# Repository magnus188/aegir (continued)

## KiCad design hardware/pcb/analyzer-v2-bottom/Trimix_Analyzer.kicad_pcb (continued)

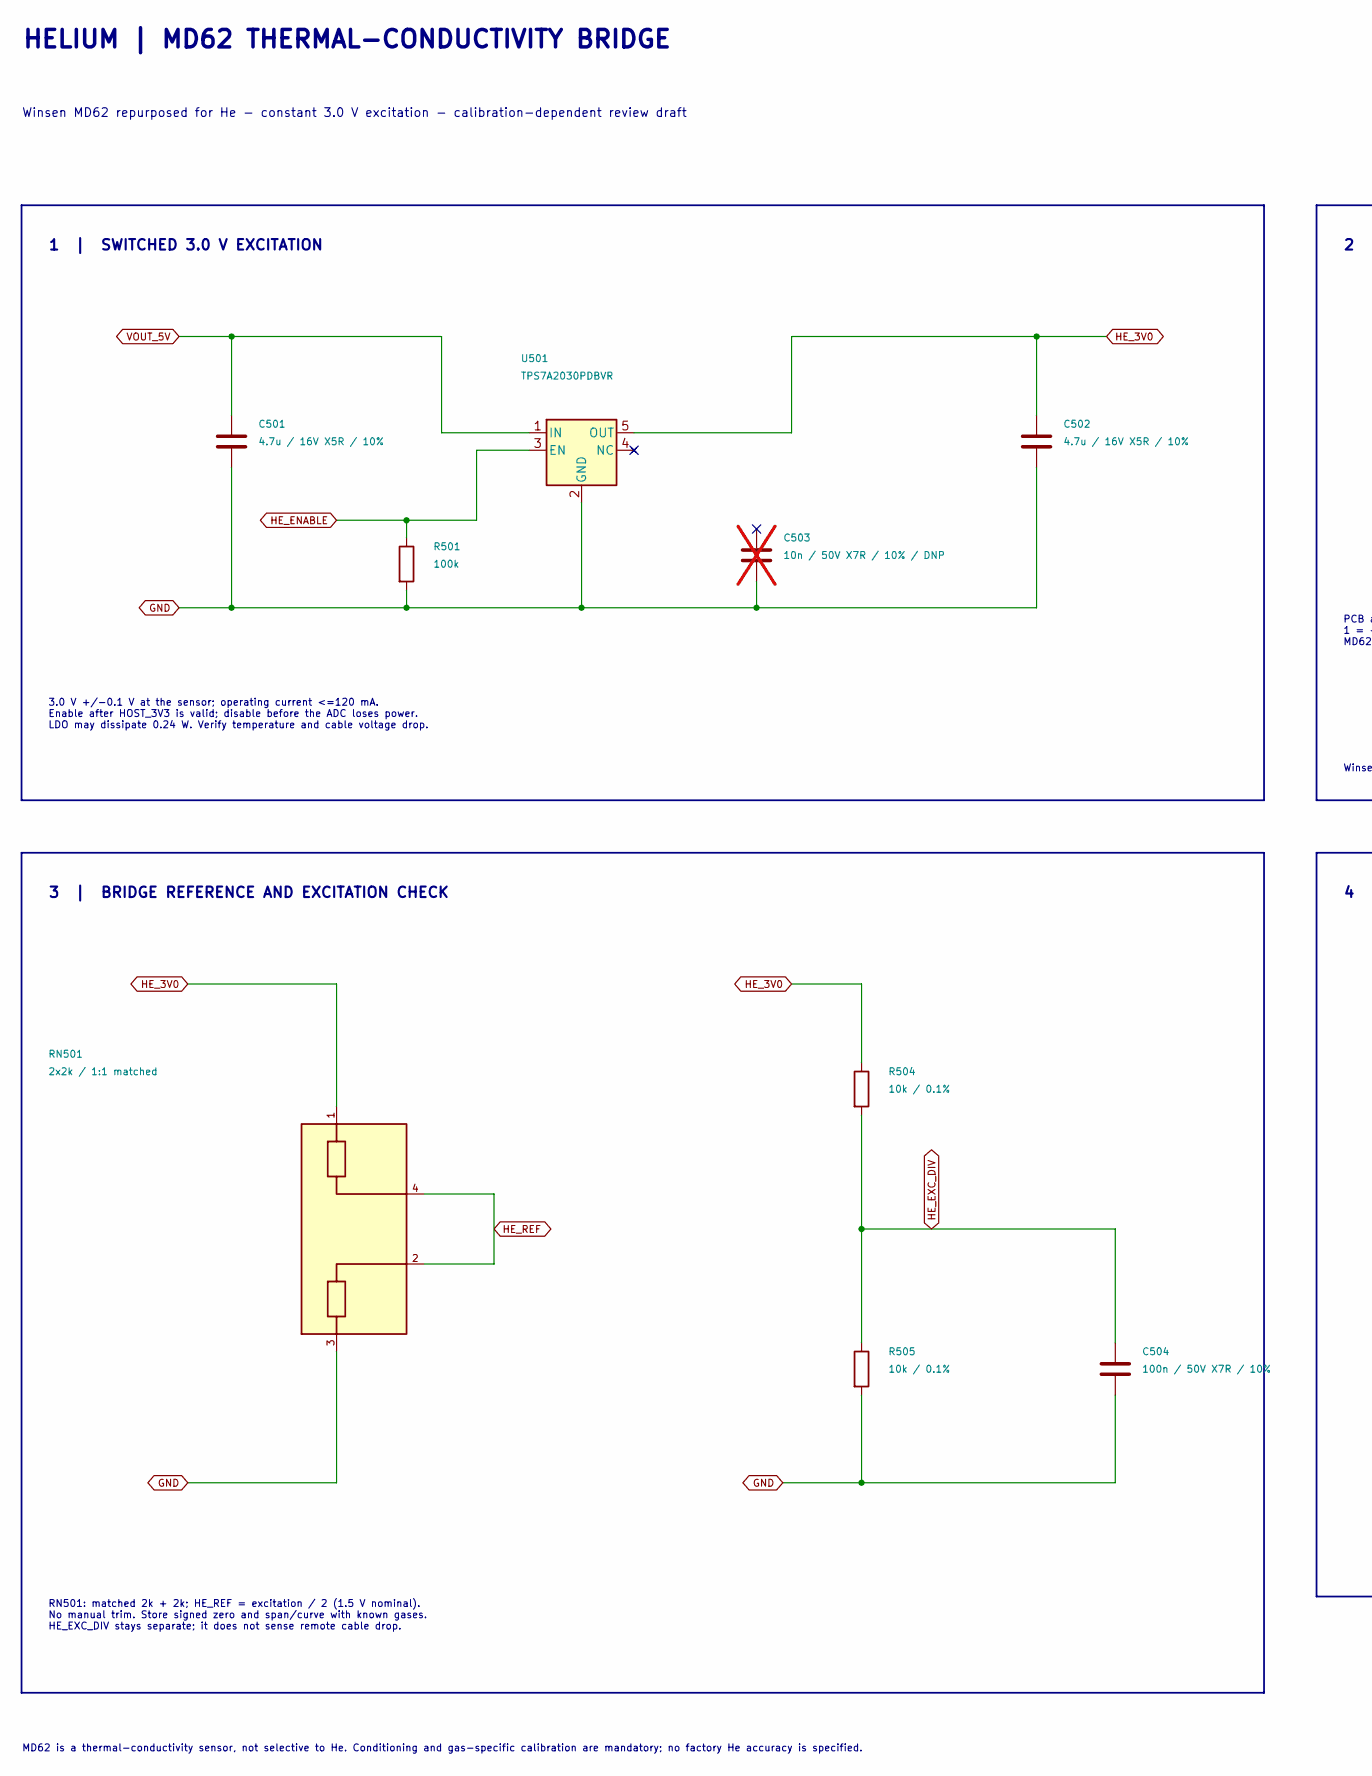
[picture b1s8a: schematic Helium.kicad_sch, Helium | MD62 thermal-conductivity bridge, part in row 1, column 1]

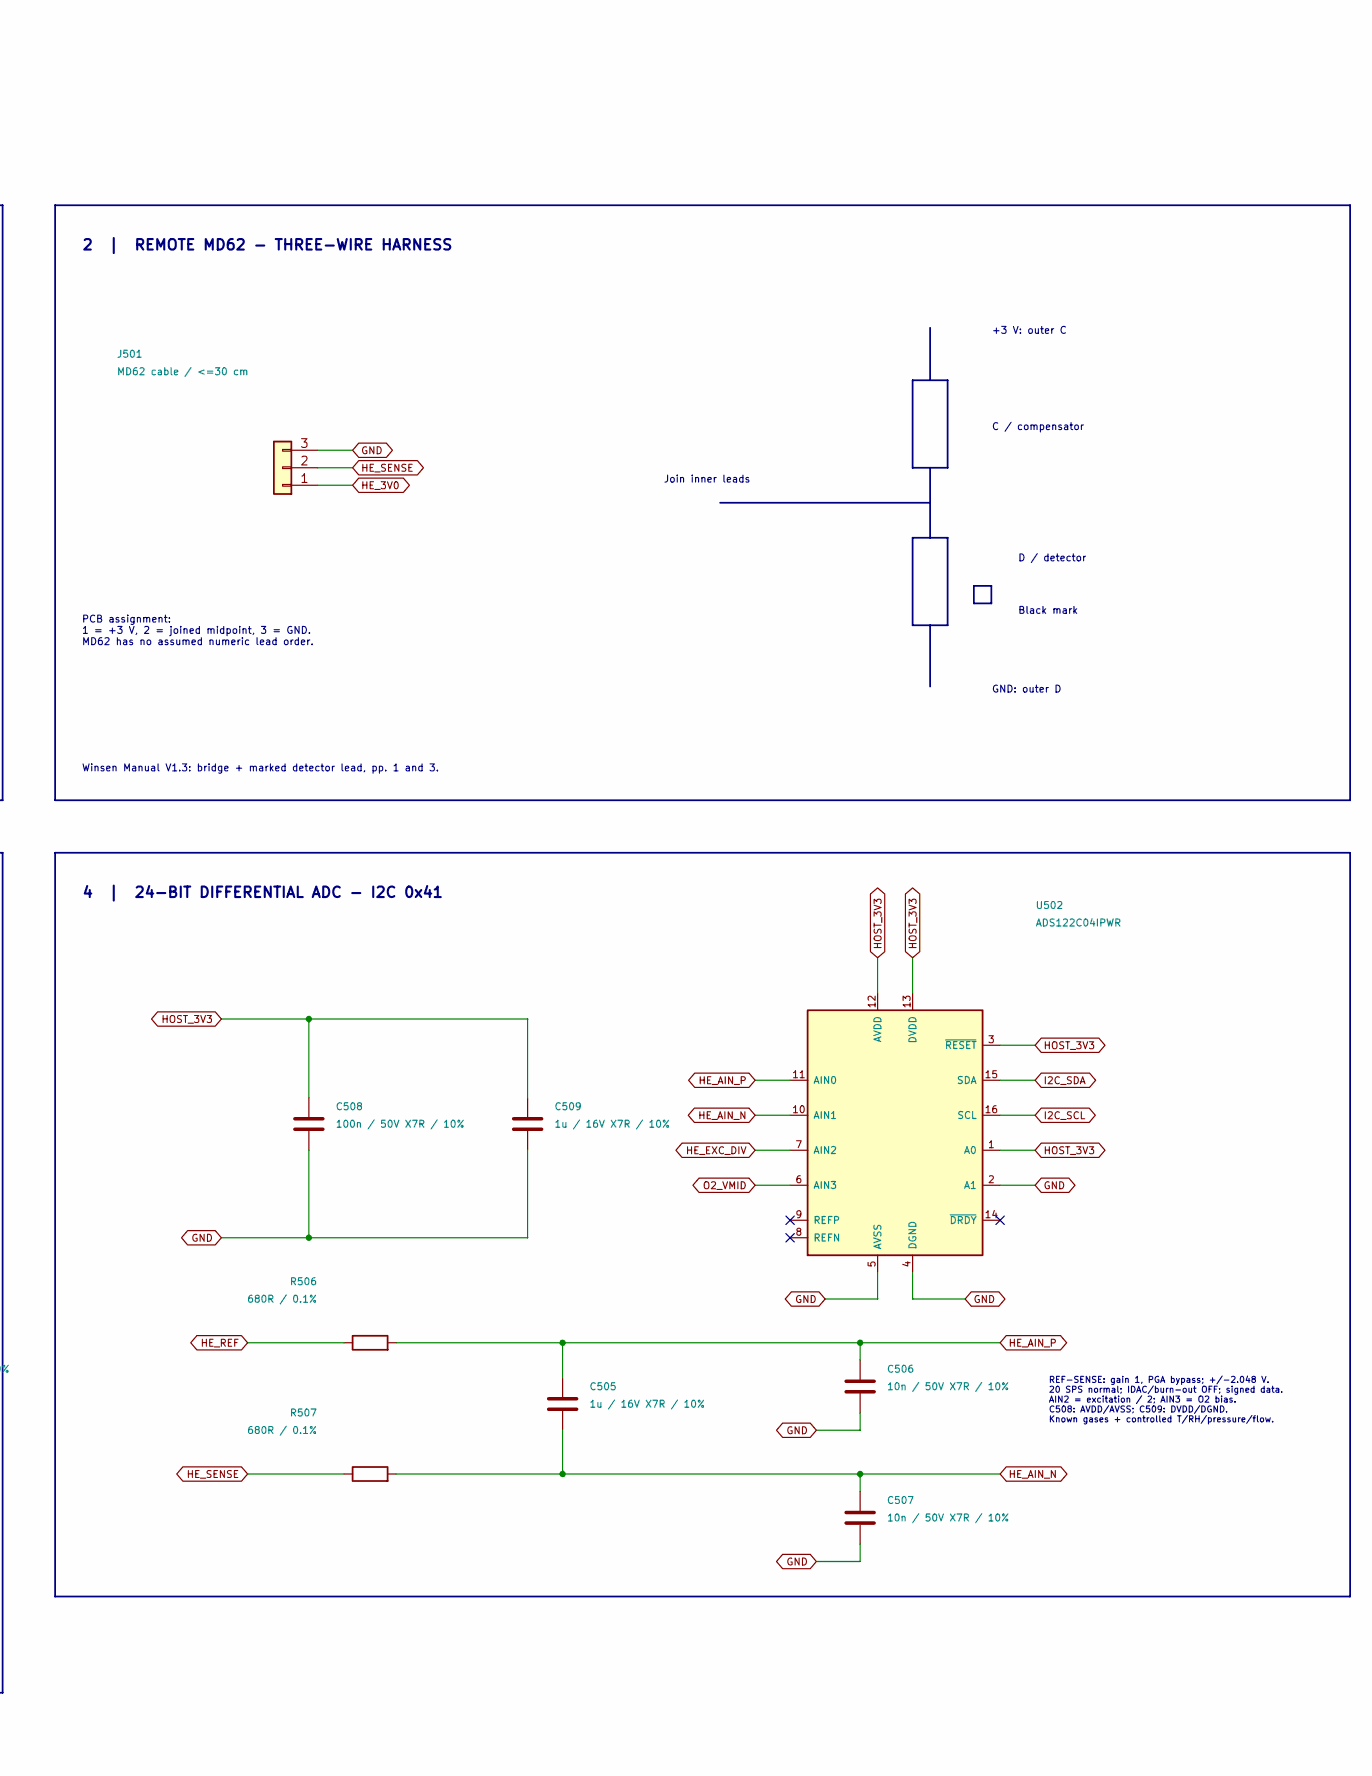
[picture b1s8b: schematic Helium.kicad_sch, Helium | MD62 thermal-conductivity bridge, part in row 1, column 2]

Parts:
C501, C502: 4.7u / 16V X5R / 10%; C_0603_1608Metric; MPN C1608X5R1C475K080AC
C503: 10n / 50V X7R / 10% / DNP; C_0603_1608Metric; MPN C1608X7R1H103K080AA; not fitted
C504, C508: 100n / 50V X7R / 10%; C_0603_1608Metric; MPN C1608X7R1H104K080AA
C505, C509: 1u / 16V X7R / 10%; C_0603_1608Metric; MPN C0603C105K4RACTU
C506, C507: 10n / 50V X7R / 10%; C_0603_1608Metric; MPN C1608X7R1H103K080AA
J501: MD62 cable / <=30 cm; PinHeader_1x03_P2.54mm_Vertical; MPN M20-9990346
R501: 100k; R_0603_1608Metric; MPN RC0603FR-07100KL
R504, R505: 10k / 0.1%; R_0603_1608Metric; MPN RT0603BRD0710KL
R506, R507: 680R / 0.1%; R_0603_1608Metric; MPN RT0603BRD07680RL
RN501: 2x2k / 1:1 matched; Vishay_ACAS0606_AT_IEC; MPN ACASN2001U2001P1AT
U501: TPS7A2030PDBVR; SOT-23-5; MPN TPS7A2030PDBVR
U502: ADS122C04IPWR; TSSOP-16_4.4x5mm_P0.65mm; MPN ADS122C04IPWR

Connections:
GND: C501.2, C502.2, C503.2, C504.2, C506.2, C507.2, C508.2, C509.2, J501.3, R501.2, R505.2, RN501.3 (R2.2), U501.2 (GND), U502.2 (A1), U502.4 (DGND), U502.5 (AVSS); also elsewhere on the board
HE_3V0: C502.1, J501.1, R504.1, RN501.1 (R1.1), U501.5 (OUT); also elsewhere on the board
HE_AIN_N: C505.2, C507.1, R507.2, U502.10 (AIN1)
HE_AIN_P: C505.1, C506.1, R506.2, U502.11 (AIN0)
HE_ENABLE: R501.1, U501.3 (EN); also elsewhere on the board
HE_EXC_DIV: C504.1, R504.2, R505.1, U502.7 (AIN2)
HE_REF: R506.1, RN501.2 (R2.1), RN501.4 (R1.2)
HE_SENSE: J501.2, R507.1; also elsewhere on the board
HOST_3V3: C508.1, C509.1, U502.1 (A0), U502.3 (~RESET), U502.12 (AVDD), U502.13 (DVDD); also elsewhere on the board
I2C_SCL: U502.16 (SCL); also elsewhere on the board
I2C_SDA: U502.15 (SDA); also elsewhere on the board
O2_VMID: U502.6 (AIN3); also elsewhere on the board
VOUT_5V: C501.1, U501.1 (IN); also elsewhere on the board

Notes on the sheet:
3.0 V +/-0.1 V at the sensor; operating current <=120 mA. Enable after HOST_3V3 is valid; disable before the ADC loses power. LDO may dissipate 0.24 W. Verify temperature and cable voltage drop.
D / detector
Black mark
REF-SENSE: gain 1, PGA bypass; +/-2.048 V. 20 SPS normal; IDAC/burn-out OFF; signed data. AIN2 = excitation / 2; AIN3 = O2 bias. C508: AVDD/AVSS; C509: DVDD/DGND. Known gases + controlled T/RH/pressure/flow.
RN501: matched 2k + 2k; HE_REF = excitation / 2 (1.5 V nominal). No manual trim. Store signed zero and span/curve with known gases. HE_EXC_DIV stays separate; it does not sense remote cable drop.
Winsen MD62 repurposed for He - constant 3.0 V excitation - calibration-dependent review draft
Join inner leads
C / compensator
2 | REMOTE MD62 - THREE-WIRE HARNESS
4 | 24-BIT DIFFERENTIAL ADC - I2C 0x41
MD62 is a thermal-conductivity sensor, not selective to He. Conditioning and gas-specific calibration are mandatory; no factory He accuracy is specified.
+3 V: outer C
PCB assignment: 1 = +3 V, 2 = joined midpoint, 3 = GND. MD62 has no assumed numeric lead order.
HELIUM | MD62 THERMAL-CONDUCTIVITY BRIDGE
GND: outer D
1 | SWITCHED 3.0 V EXCITATION
Winsen Manual V1.3: bridge + marked detector lead, pp. 1 and 3.
3 | BRIDGE REFERENCE AND EXCITATION CHECK

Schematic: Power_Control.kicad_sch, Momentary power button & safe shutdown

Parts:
C801, C802: 100n / 50V X7R / 10%; C_0603_1608Metric; MPN C1608X7R1H104K080AA
C803: 33n / 50V X7R / 10%; C_0805_2012Metric; MPN C0805C333K5RACTU
C804: 1u / 16V X7R / 10%; C_0603_1608Metric; MPN C0603C105K4RACTU
J801: POWER BUTTON / 1NO; PinHeader_1x02_P2.54mm_Vertical; MPN M20-9990246
J802: BUTTON LED +/-; PinHeader_1x02_P2.54mm_Vertical; MPN M20-9990246
R801: 5.1k; R_0603_1608Metric; MPN RC0603FR-075K1L
R802: 10k; R_0603_1608Metric; MPN RC0603FR-0710KL
R803: 100k; R_0603_1608Metric; MPN RC0603FR-07100KL
R804: 1k / DNP; R_0603_1608Metric; MPN RC0603FR-071KL; not fitted
U801: LTC2954CTS8-1; TSOT-23-8; MPN LTC2954CTS8-1#TRMPBF

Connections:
BUTTON_LED_A: J802.1, R804.2
GND: C801.2, C802.2, C803.2, C804.2, J801.2, J802.2, U801.4 (GND); also elsewhere on the board
HOST_3V3: R802.1, R803.1; also elsewhere on the board
unnamed: J801.1, R801.1
unnamed: C803.1, U801.3 (ONT)
unnamed: C804.1, U801.7 (PDT)
PB_FILTERED_N: C802.1, R801.2, U801.2 (~PB)
POWER_EN: U801.6 (EN); also elsewhere on the board
POWER_INT_N: R802.2, U801.5 (~INT); also elsewhere on the board
POWER_KILL_N: R803.2, U801.8 (~KILL); also elsewhere on the board
VOUT_5V: R804.1; also elsewhere on the board
VSYS: C801.1, U801.1 (VIN); also elsewhere on the board

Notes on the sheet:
02 ALWAYS-ON POWER LATCH
01 PANEL BUTTON & INPUT FILTER
The button switches the 5 V load. The armed charger remains available with the screen and sensors off.
04 BUTTON SEQUENCE & IMPLEMENTATION
J801 carries only the isolated switch contacts. The separate LED wires go to J802. Place R801/C802 close to U801. A normally-open contact closes PB to ground.
05 SEPARATE BUTTON LED
MOMENTARY POWER BUTTON & SAFE SHUTDOWN
GPIO32 reads the debounced active-low interrupt. GPIO33 releases KILL during boot and normal use. After saving state, drive KILL low to turn off. Configure GPIO33 as open-drain; avoid a low glitch. R803 uses the switched 3.3 V rail so startup does not depend on firmware asserting an early hold.
HOST_3V3 must rise within the 400 ms minimum startup blanking period; verify on real hardware.
03 HOST SHUTDOWN HANDSHAKE
OFF: press for about 0.25 s; the converter, Guition and sensors turn on. ON: firmware should treat a deliberate press as a shutdown request, stop sensing, save state, then pull POWER_KILL_N low. This firmware is not implemented yet. A continuous ~6.5 s hold forces off even if the host hangs. Timing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
R804 initially DNP. Verify the ordered LED voltage, built-in resistor and polarity before fitting a value.
ONT: about 0.245 s to switch on. PDT: about 6.5 s held to force off. R203 on sheet 3 supplies the EN pull-up.

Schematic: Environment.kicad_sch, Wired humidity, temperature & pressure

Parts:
C601: 1u / 25V X7R / 10%; C_0805_2012Metric; MPN C2012X7R1E105K125AB
J601: BME280 harness; JST_XH_B4B-XH-A_1x04_P2.50mm_Vertical; MPN B4B-XH-A(LF)(SN)
Q601, Q602: BSS138; SOT-23; MPN BSS138-7-F
R601: 0R / fit: 3.3 V; R_0603_1608Metric; MPN RC0603JR-070RL
R602: 0R / DNP: 5 V option; R_0603_1608Metric; MPN RC0603JR-070RL; not fitted
R603, R604: 4.7k / DNP; R_0603_1608Metric; MPN RC0603FR-074K7L; not fitted
U601: GYBMEP / BME280-5V

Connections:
BME_SCL: J601.3 (SCL), Q601.3 (D), R603.2, U601.3 (SCL)
BME_SDA: J601.4 (SDA), Q602.3 (D), R604.2, U601.4 (SDA)
BME_VIN: C601.1, J601.1 (VIN), R601.2, R602.2, R603.1, R604.1, U601.1 (VIN)
GND: C601.2, J601.2 (GND), U601.2 (GND); also elsewhere on the board
HOST_3V3: Q601.1 (G), Q602.1 (G), R601.1; also elsewhere on the board
I2C_SCL: Q601.2 (S); also elsewhere on the board
I2C_SDA: Q602.2 (S); also elsewhere on the board
VOUT_5V: R602.1; also elsewhere on the board

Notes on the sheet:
02 I2C LEVEL INTERFACE
GYBMEP module in the vented gas chamber. Four-wire harness, maximum 30 cm; dedicated sensor I2C at 100 kHz.
03 PCB HARNESS CONNECTION
05 REMOTE MODULE IN THE CHAMBER
Main PCB: JST-XH, 2.50 mm, 4 positions. Wire to the module labels, not its board colour. VIN / GND / SCL / SDA, as photographed. Use strain relief at both cable ends.
Fit only R601 initially. Never fit both links. R602 requires a verified 5 V VIN module. Check the module regulator output and pull-ups before choosing an alternate supply.
U601 is off-board; only J601 is mounted on the main PCB. Keep the sensor away from the MD62 heater and regulator. Use a regulated, vented chamber near atmospheric pressure. Allow gas contact with the sensor opening; prevent condensation. This chamber sensor does not replace the battery thermistor.
1. Read chip ID register 0xD0: BME280 must return 0x60. BMP280 does not measure humidity. Probe 0x76 and 0x77. 2. Verify the actual module VDD / VDDIO and pull-up rail. Chip limits: VDD 1.71-3.6 V; VDDIO 1.2-3.6 V. The product photograph does not prove the fitted regulator. 3. R603/R604 are unpopul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
WIRED HUMIDITY, TEMPERATURE & PRESSURE
04 COMMISSIONING & SIGNAL INTEGRITY
01 MODULE POWER SELECTION

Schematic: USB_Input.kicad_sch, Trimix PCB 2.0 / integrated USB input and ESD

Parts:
D901: TPD1E10B06DYAR; TI_DYA0002A; MPN TPD1E10B06DYAR
J901: USB4105-GF-A; USB_C_Receptacle_GCT_USB4105_GF_A_GroundLandOffset025; MPN USB4105-GF-A
J902: TO MAIN J101 | SAME PIN NUMBERS; USB_Harness_6P_P1.8mm
U901: TPD4E05U06DQAR; TI_DQA0010B; MPN TPD4E05U06DQAR

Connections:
GND: D901.2 (GND), J901.A1 (GND), J901.A12 (GND), J901.B1 (GND), J901.B12 (GND), J901.SH (SHIELD), J902.2, U901.3 (GND), U901.8 (GND); also elsewhere on the board
USB_5V: D901.1 (VBUS), J901.A4 (VBUS), J901.A9 (VBUS), J901.B4 (VBUS), J901.B9 (VBUS), J902.1; also elsewhere on the board
USB_CC1: J901.A5 (CC1), J902.3, U901.1 (CC1), U901.10 (NC_/_PCB_link); also elsewhere on the board
USB_CC2: J901.B5 (CC2), J902.4, U901.2 (CC2), U901.9 (NC_/_PCB_link); also elsewhere on the board
USB_D_M: J901.A7 (D-), J901.B7 (D-), J902.6, U901.5 (D-), U901.6 (NC_/_PCB_link); also elsewhere on the board
USB_D_P: J901.A6 (D+), J901.B6 (D+), J902.5, U901.4 (D+), U901.7 (NC_/_PCB_link); also elsewhere on the board

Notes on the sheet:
01 USB-C RECEPTACLE | PCB 2.0
03 NET REFERENCES | J101/J902 NOT FITTED
TRIMIX PCB 2.0 | USB-C + EXISTING ESD CIRCUIT
Integrated 4-layer / 1.6 mm main PCB. Nominal 5 V input; USB-C attachment and BC1.2 detection are unchanged.
02 FOUR-LINE + VBUS ESD PROTECTION
No internal links on pins6/7/9/10. PCB copper joins 1-10(CC1),2-9(CC2),4-7(D+),5-6(D-). D901 surge clamp exceeds 6 V: upstream transient coordination remains a main-system requirement.
USB4105-GF-A top mount; no daughterboard or harness. GND lands offset 0.025 mm; supplier DFM approval pending. Factory stencil/reflow for U901 and connector shell slots. Support the new PCB tab and socket inside the revised case. No 9/12/20 V request; test both cable orientations, source change, ho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
Net references only: no harness is assembled in PCB 2.0. 1 = USB_5V 2 = GND 3 = CC1 4 = CC2 5 = D+ 6 = D- No extra Rd: existing TUSB320LAI supplies termination.
04 ASSEMBLY AND QUALIFICATION
Shield and all ground contacts join GND. A6/B6 join D+; A7/B7 join D-. SBU is NC. No local Rd: TUSB320LAI on main PCB supplies Rd.

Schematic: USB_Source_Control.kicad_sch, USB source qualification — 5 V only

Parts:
C110, C111, C112, C113: 100n / 50V X7R / 10%; C_0603_1608Metric; MPN C1608X7R1H104K080AA
Q110: DMN2056U-7; DMN2056U_SOT23_Diodes_Recommended; MPN DMN2056U-7
Q111: DMN2056U-7; SOT-23; MPN DMN2056U-7
R110: 887k / 1%; R_0603_1608Metric; MPN RC0603FR-07887KL
R111: 33k / 1%; R_0603_1608Metric; MPN RC0603FR-0733KL
R112: 10k / 1%; R_0603_1608Metric; MPN RC0603FR-0710KL
R113: 97.6k / 0.1%; R_0603_1608Metric; MPN RT0603BRD0797K6L
R114: 10k / 0.1%; R_0603_1608Metric; MPN RT0603BRD0710KL
R115: 10k / 0.1%; R_0402_1005Metric; Voltage_rating_note Continuous voltage also limited by dera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; MPN RT0402BRD0710KL
R116: 1k / 0.1%; R_0603_1608Metric; MPN RT0603BRD071KL
R117: 100k / 1%; R_0603_1608Metric; MPN RC0603FR-07100KL
R118: 100k / 0.1%; R_0402_1005Metric; Voltage_rating_note Continuous voltage also limited by dera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; MPN RT0402BRD07100KL
U110: TUSB320LAIRWBR; Texas_X2QFN-12_1.6x1.6mm_P0.4mm; MPN TUSB320LAIRWBR
U111: PI3USB9201ZTAEX; PI3USB9201_UQFN2020_12_TypeC; MPN PI3USB9201ZTAEX
U112: SN74AUP1G74DCUR; VSSOP-8_2.3x2mm_P0.5mm; MPN SN74AUP1G74DCUR
U113: TPS3808G01DBVR; SOT-23-6; MPN TPS3808G01DBVR

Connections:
GND: C110.2, C111.2, C112.2, C113.2, Q111.2 (S), R114.2, R117.2, R118.2, U110.3 (PORT), U110.5 (ADDR), U110.10 (GND), U110.11 (EN_N), U111.9 (GND), U111.10 (ADDR), U111.11 (ENB), U112.4 (GND), U113.2 (GND); also elsewhere on the board
HOST_3V3: C110.1, C111.1, C112.1, C113.1, R111.1, R112.1, R115.1, U110.12 (VDD), U111.12 (VDD), U112.2 (D), U112.7 (PRE_N), U112.8 (VCC), U113.6 (VDD); also elsewhere on the board
I2C_SCL: U110.8 (SCL), U111.3 (SCL); also elsewhere on the board
I2C_SDA: U110.7 (SDA), U111.4 (SDA); also elsewhere on the board
USB_5V: R110.1; also elsewhere on the board
USB_BC_INT_N: R112.2, U111.5 (INTB)
USB_CC1: U110.1 (CC1); also elsewhere on the board
USB_CC2: U110.2 (CC2); also elsewhere on the board
USB_CC_INT_N: R111.2, U110.6 (INT_N), U113.3 (MR); also elsewhere on the board
USB_D_M: U111.7 (D-); also elsewhere on the board
USB_D_P: U111.8 (D+); also elsewhere on the board
USB_ILIM_AUTH: Q111.1 (G), R117.1, U112.1 (CLK); also elsewhere on the board
USB_ILIM_BRANCH: Q110.3 (D), R116.2
USB_ILIM_SERIES: Q110.2 (S), Q111.3 (D)
USB_LIMIT_SET: R116.1; also elsewhere on the board
USB_OVP_5V: R113.1; also elsewhere on the board
USB_PERMISSION_CLR_N: R115.2, U112.6 (CLR_N), U113.1 (RESET)
USB_PERMISSION_Q: Q110.1 (G), R118.1, U112.5 (Q)
USB_PERMISSION_Q_N: U112.3 (Q_N); also elsewhere on the board
USB_VBUS_DET: R110.2, U110.4 (VBUS_DET)
USB_VBUS_SENSE: R113.2, R114.1, U113.5 (SENSE)

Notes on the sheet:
100 mA hardware default. Higher input permission requires a qualified source and a fresh host authorization edge.
02 USB-A / BC1.2 DETECTOR / I2C 0x5F
01 USB-C SINK / INTERNAL Rd / I2C 0x47
USB SOURCE QUALIFICATION — 5 V ONLY
R901/R902 on the USB board are DNP: U110 supplies both Rd terminations. Unpowered CC pins retain dead-battery Rd. PORT/ADDR/EN_N are hard-grounded.
GPIO50 / J301.11: LOW selects nominal50mA; a qualified rising edge authorizes. U114 on sheet13 provides the input limit. R116 switches its parallel1k branch. Both FETs must be ON. A CC/VBUS reset requires a new host LOW→HIGH. BQ current register must still match the valid source budget. CHARGE ARM 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
TPS3808 is powered by HOST_3V3, separately senses USB VBUS. Nominal falling threshold 4.358 V; corner threshold calculation in review. CT open: release delay 12–28 ms. Wait at least 30 ms after CC IRQ clear. Loss/CC change forces Q low even if the host GPIO remains stuck high. Power-up RESET is ass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
04 FRESH AUTHORIZATION EDGE / HARDWARE CURRENT CEILING
03 INDEPENDENT VBUS LOSS + CC RESET + STARTUP
Client mode only. D+/D- never connect to the BQ25895. No PD or HVDCP. Read-and-clear BC status only while host permission is LOW. No USB data path.

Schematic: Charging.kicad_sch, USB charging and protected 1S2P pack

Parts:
C101: 1u / 16V X7R / 10%; C_0603_1608Metric; MPN C0603C105K4RACTU
C102, C104, C105: 22u / 16V X7R / 20%; C_1210_3225Metric; MPN C3225X7R1C226M250AC
C103: 47n / 50V X7R / 10%; C_TDK_C1005_Recommended; MPN C1005X7R1H473K050BE
C106: 22u / 25V X5R / 20%; C_1206_3216Metric; MPN C3216X5R1E226M160AB
C107: 47u / 10V X5R / 20%; C_TDK_C2012_Recommended; MPN C2012X5R1A476M125AC
C108: 4.7u / 16V X5R / 10%; C_0603_1608Metric; MPN C1608X5R1C475K080AC
J101: USB HARNESS: 5V/GND/CC1/CC2/D+/D-; USB_Harness_6P_P1.8mm
J102: PACK PIGTAIL; Battery_Pigtail_2x22AWG_P4.2_D1.00_Pad1.85
J103: PACK NTC: 103AT-2; PinHeader_1x02_P2.54mm_Vertical; MPN M20-9990246
J104: ARM: OPEN; PinHeader_1x02_P2.54mm_Vertical; MPN M20-9990246
L101: 1u / 74437349010; L_Wurth_74437349010_7050; MPN 74437349010
Q101: 2N7002; SOT-23; MPN 2N7002-7-F
R101: 5.23k 1%; R_0402_1005Metric; Voltage_rating_note Continuous voltage also limited by dera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; MPN RC0402FR-075K23L
R102: 30.1k 1%; R_0603_1608Metric; MPN RC0603FR-0730K1L
R103: 300R / 1% / supported ILIM range; R_0603_1608Metric; MPN RC0603FR-07300RL
R104, R105: 100k; R_0603_1608Metric; MPN RC0603FR-07100KL
R107: 10k; R_0603_1608Metric; MPN RC0603FR-0710KL
TP1013: CHG_STAT_N; TestPoint_Pad_D0.8mm
TP1014: QON SERVICE; TestPoint_Pad_D0.8mm
U101: BQ25895RTWR; TI_RTW24_4x4_ThermalVias_ServicePad; MPN BQ25895RTWR

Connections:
/01 CHARGING + BATTERY/BQ_BTST: C103.2, U101.21 (BTST)
/01 CHARGING + BATTERY/BQ_PMID: C102.1, U101.23 (PMID)
/01 CHARGING + BATTERY/BQ_QON_N: TP1014.1, U101.12 (~QON)
/01 CHARGING + BATTERY/BQ_REGN: C107.1, R101.1, U101.22 (REGN)
/01 CHARGING + BATTERY/BQ_SW: C103.1, L101.1, U101.19 (SW), U101.20 (SW)
/01 CHARGING + BATTERY/CHG_CE_N: Q101.3 (D), R104.2, U101.9 (~CE)
/01 CHARGING + BATTERY/CHG_STAT_N: TP1013.1, U101.4 (STAT)
/01 CHARGING + BATTERY/PACK_TS: J103.1, R101.2, R102.1, U101.11 (TS)
BQ_ILIM: R103.1, U101.10 (ILIM)
CHARGE_ARM: J104.2 (B), Q101.1 (G), R105.1
CHG_INT_N: R107.2, U101.7 (~INT); also elsewhere on the board
GND: C101.2, C102.2, C104.2, C105.2, C106.2, C107.2, C108.2, J101.2, J102.2, J103.2, Q101.2 (S), R102.2, R103.2, R105.2, U101.8 (OTG), U101.17 (PGND), U101.18 (PGND), U101.25 (PGND); also elsewhere on the board
HOST_3V3: R107.1; also elsewhere on the board
I2C_SCL: U101.5 (SCL); also elsewhere on the board
I2C_SDA: U101.6 (SDA); also elsewhere on the board
PACK_P: C106.1, J102.1, U101.13 (BAT), U101.14 (BAT); also elsewhere on the board
USB_CHG_5V: C101.1, U101.1 (VBUS); also elsewhere on the board
VSYS: C104.1, C105.1, C108.1, J104.1 (A), L101.2, R104.1, U101.15 (SYS), U101.16 (SYS); also elsewhere on the board

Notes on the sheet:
05 COMMISSIONING ARM & SERVICE WAKE
C108 supplements the retained C104/C105 SYS bulk. TP1013 exposes charger STAT on the board rear. R107 pulls charger/permission feedback up to 3.3 V.
Follow the top row from USB input to charger and battery. The lower row controls and monitors charging.
02 CHARGER & POWER PATH
Charging & protected battery
01 USB INPUT
03 PROTECTED BATTERY
TRIMIX / ANALYZER ELECTRONICS / SHEET 2
Matching labels connect electrically. VSYS also supplies the always-on pushbutton controller. BQ25895 I2C address = 0x6A. If firmware writes settings, disable its watchdog before host shutdown. Default settings return after complete charger power loss. Keep J104 OPEN until those settings are qualif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
R101/R102 and the external 10k NTC sense temperature. Attach the NTC to the cells; connect it at J103. An open sensor inhibits charging.
J104 OPEN = charging disabled; R105 holds Q101 off. Fit the shunt only after cell/USB/NTC validation. Armed = autonomous charging with the host ON or OFF. TP1014 = local QON service access; use TP1001 GND.
04 PACK TEMPERATURE
J101 receives 5 V from the GCT USB daughterboard. J902 -> two-wire harness -> J101 (same pin numbers). See USB_Input, sheet 10; qualify before charging.
Autonomous defaults: 4.208 V, 2.048 A charge setting. Floating D+/D- selects 500 mA input; actual charge current falls to match input power. ILIM: 300R (~0.57 A). No charger firmware is implemented; defaults need review.
06 STATUS INDICATORS
J102 = PCB pigtail to the RCY/BEC cable mate. Red = protected P+; black = protected P-. FMA holder: 2 x 3400 mAh in parallel, 6800 mAh total. Verify polarity; no PCB-mounted RCY footprint is implied.
READING THIS SHEET

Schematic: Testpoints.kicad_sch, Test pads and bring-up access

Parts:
TP1001: GND; TestPoint_Pad_D1.0mm
TP1002: USB_5V; TestPoint_Pad_D1.0mm
TP1003: PACK_P; TestPoint_Pad_D1.0mm
TP1004: VSYS; TestPoint_Pad_D1.0mm
TP1005: VOUT_5V; TestPoint_Pad_D1.0mm
TP1006: HOST_3V3; TestPoint_Pad_D1.0mm
TP1007: POWER_EN; TestPoint_Pad_D1.0mm
TP1008: I2C_SCL; TestPoint_Pad_D1.0mm
TP1009: I2C_SDA; TestPoint_Pad_D1.0mm
TP1010: HE_3V0; TestPoint_Pad_D1.0mm
TP1011: HE_SENSE; TestPoint_Pad_D1.0mm
TP1012: O2_VMID; TestPoint_Pad_D1.0mm

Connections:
GND: TP1001.1 (1_1); also elsewhere on the board
HE_3V0: TP1010.1 (1_1); also elsewhere on the board
HE_SENSE: TP1011.1 (1_1); also elsewhere on the board
HOST_3V3: TP1006.1 (1_1); also elsewhere on the board
I2C_SCL: TP1008.1 (1_1); also elsewhere on the board
I2C_SDA: TP1009.1 (1_1); also elsewhere on the board
O2_VMID: TP1012.1 (1_1); also elsewhere on the board
PACK_P: TP1003.1 (1_1); also elsewhere on the board
POWER_EN: TP1007.1 (1_1); also elsewhere on the board
USB_5V: TP1002.1 (1_1); also elsewhere on the board
VOUT_5V: TP1005.1 (1_1); also elsewhere on the board
VSYS: TP1004.1 (1_1); also elsewhere on the board

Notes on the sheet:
PROBE ACCESS
03 BUS AND SENSOR SIGNALS
Use TP1001 as the circuit ground reference. HE_SENSE and O2_VMID require a high-impedance probe.
Place pads where a probe can reach them after opening the rear cover. Label each pad on silkscreen.
01 BATTERY AND USB
Verify pad locations, clearances and physical test access on the PCB; this page adds no circuit bias or switches.
02 HOST POWER AND CONTROL
Twelve bare 1.0 mm copper pads. Matching global labels connect to the existing circuit pages.
Do not bridge adjacent pads. Keep the charge-arm shunt open during initial power checks.
TRIMIX / TEST PADS AND BRING-UP ACCESS

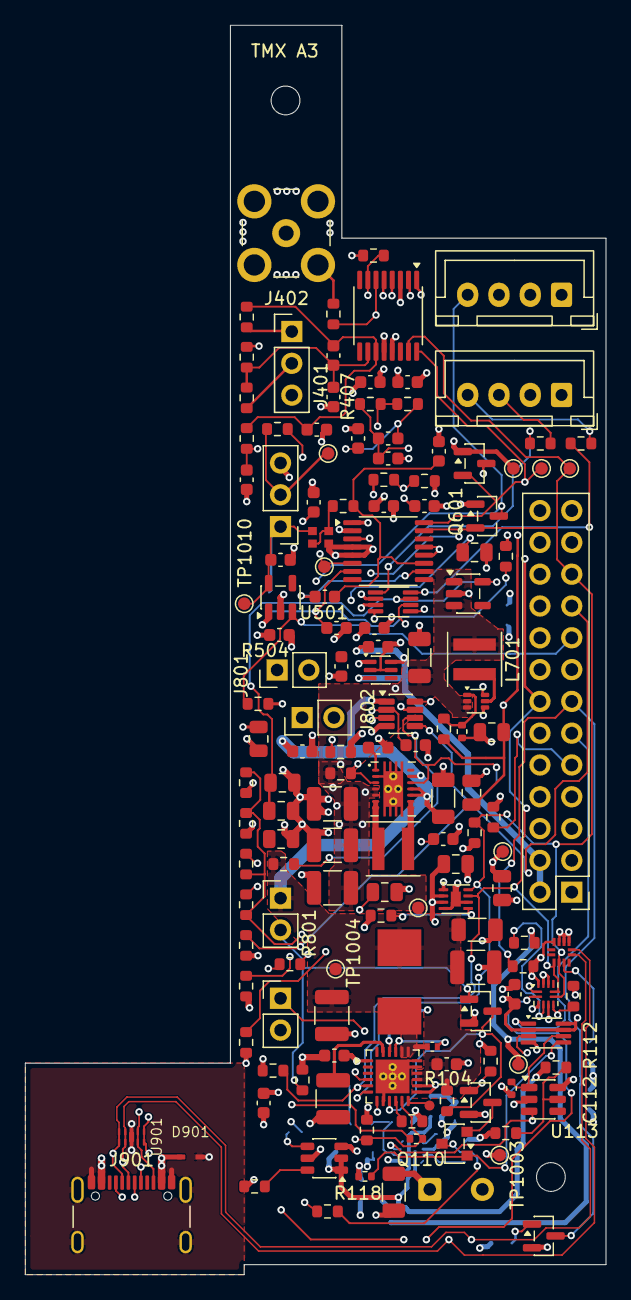
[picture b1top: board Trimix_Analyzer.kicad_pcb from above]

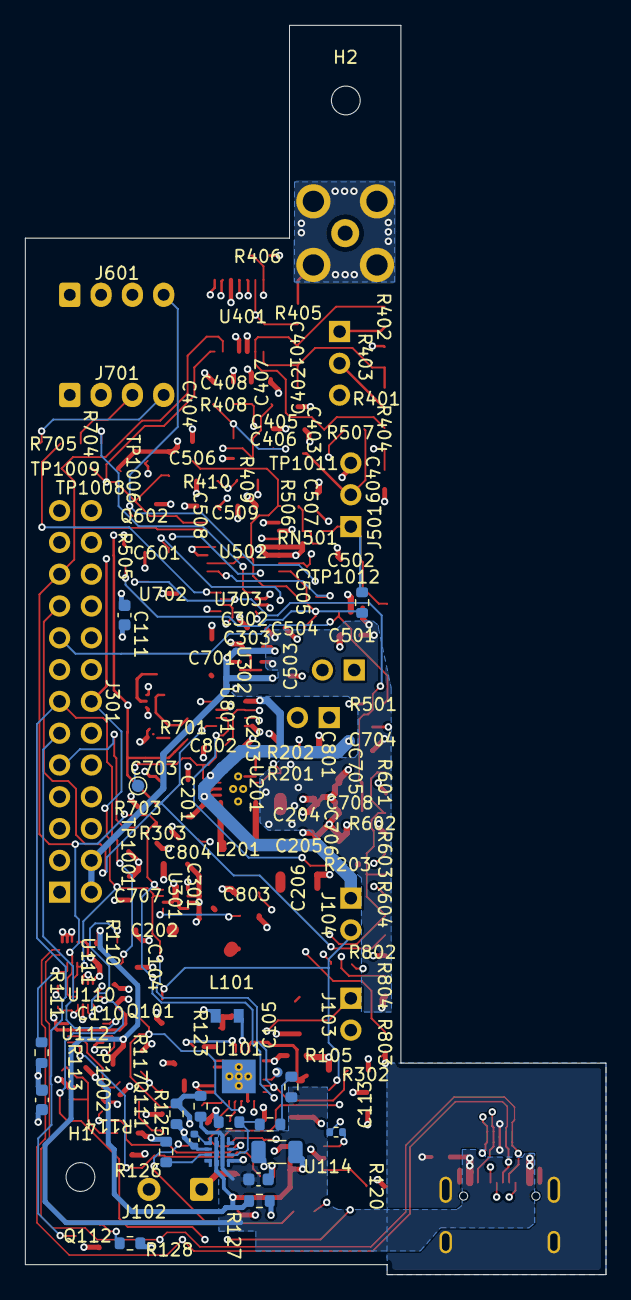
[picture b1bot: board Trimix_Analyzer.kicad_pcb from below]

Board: 4 copper layers, 46.4 x 99.8 mm, 171 parts (20 on the bottom side), 86 nets.

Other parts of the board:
H1, H2: M2 NPTH 2.30; Mechanical_M2_NPTH_2.30mm

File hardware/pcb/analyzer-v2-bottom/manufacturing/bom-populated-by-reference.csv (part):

Reference,Value,Manufacturer,MPN,Quantity,Population_quantity,Category,Footprint,Side,PCB_X_mm,PCB_Y_mm,Rotation_deg,Assembly_note,Native_exclude_from_BOM,Native_exclude_from_CPL
C101,1u / 16V X7R / 10%,KEMET / YAGEO,C0603C105K4RACTU,1,1,Populate,C_0603_1608Metric,top,28.2,103.78491,180,,False,False
C102,22u / 16V X7R / 20%,TDK,C3225X7R1C226M250AC,1,1,Populate,C_1210_3225Metric,top,28,100.58491,90,,False,False
C103,47n / 50V X7R / 10%,TDK,C1005X7R1H473K050BE,1,1,Populate,C_TDK_C1005_Recommended,top,36.025,103.075,0,Factory reflow for true0402; recommendedTDK lands; supplierprocess qualification remains required,False,False
C104,22u / 16V X7R / 20%,TDK,C3225X7R1C226M250AC,1,1,Populate,C_1210_3225Metric,top,39.5,96.73491,0,,False,False
C105,22u / 16V X7R / 20%,TDK,C3225X7R1C226M250AC,1,1,Populate,C_1210_3225Metric,top,28.099999,107.23491,90,,False,False
C106,22u / 25V X5R / 20%,TDK,C3216X5R1E226M160AB,1,1,Populate,C_1206_3216Metric,top,22.85,112.23491,0,,False,False
C107,47u / 10V X5R / 20%,TDK,C2012X5R1A476M125AC,1,1,Populate,C_TDK_C2012_Recommended,bottom,33.775,100.60991,0,Factory reflow recommended for rear local REGN capacitor and manufacturer reflow lands; supplier process qualification remains open.,False,False
C108,4.7u / 16V X5R / 10%,TDK,C1608X5R1C475K080AC,1,1,Populate,C_0603_1608Metric,top,37.075,104.5,0,,False,False
C110,100n / 50V X7R / 10%,TDK,C1608X7R1H104K080AA,1,1,Populate,C_0603_1608Metric,top,42.6,98.88491,90,,False,False
C111,100n / 50V X7R / 10%,TDK,C1608X7R1H104K080AA,1,1,Populate,C_0603_1608Metric,bottom,48.7,94,90,,False,False
C112,100n / 50V X7R / 10%,TDK,C1608X7R1H104K080AA,1,1,Populate,C_0603_1608Metric,bottom,48.575,107.325,-90,,False,False
C113,100n / 50V X7R / 10%,TDK,C1608X7R1H104K080AA,1,1,Populate,C_0603_1608Metric,bottom,48.525,103.525,90,,False,False
C114,4.7u / 25V X7R / 10%,TDK,C3216X7R1E475K160AC,1,1,Populate,C_1206_3216Metric,bottom,29.8,111.48491,0,,False,False
C115,100n / 50V X7R,TDK,C1608X7R1H104K080AA,1,1,Populate,C_0603_1608Metric,bottom,31.9,114.23491,-90,,False,False
C116,3.3n / 50V C0G / 5%,Murata,GRM1555C1H332JE01D,1,1,Populate,C_0402_1005Metric,bottom,36.4,110.53491,-90,Factory reflow for true 0402 part; 3.3nF C0G slew timing function unchanged; exact BOM/CPL quote required,False,False
C201,22u / 25V X5R / 20%,TDK,C3216X5R1E226M160AB,1,1,Populate,C_1206_3216Metric,top,36.9,83.23491,90,,False,False
C202,22u / 25V X5R / 20%,TDK,C3216X5R1E226M160AB,1,1,Populate,C_1206_3216Metric,top,39.6,93.73491,0,,False,False
C203,100n / 50V X7R / 10%,TDK,C1608X7R1H104K080AA,1,1,Populate,C_0603_1608Metric,top,31.7,79.18491,0,,False,False
C204,22u / 16V X7R / 20%,TDK,C3225X7R1C226M250AC,1,1,Populate,C_1210_3225Metric,top,28.05,83.675,180,,False,False
C205,22u / 16V X7R / 20%,TDK,C3225X7R1C226M250AC,1,1,Populate,C_1210_3225Metric,top,28.05,86.98491,180,,False,False
C206,22u / 16V X7R / 20%,TDK,C3225X7R1C226M250AC,1,1,Populate,C_1210_3225Metric,top,28.05,90.38491,180,,False,False
C301,100n / 50V X7R / 10%,KEMET / YAGEO,C0805C104K5RACTU,1,1,Populate,C_0805_2012Metric,top,37.9,88.48491,0,,False,False
C302,4.7u / 16V X5R / 10%,TDK,C1608X5R1C475K080AC,1,1,Populate,C_0603_1608Metric,top,31.4,69.58491,0,,False,False
C303,4.7u / 16V X5R / 10%,TDK,C1608X5R1C475K080AC,1,1,Populate,C_0603_1608Metric,top,31.9,71.13491,0,,False,False
C401,1u / 16V X7R / 10%,KEMET / YAGEO,C0603C105K4RACTU,1,1,Populate,C_0603_1608Metric,top,28.125,47.85991,90,,False,False
C402,10n / 50V X7R / 10%,TDK,C1608X7R1H103K080AA,1,1,Populate,C_0603_1608Metric,top,28.125,51.175,-90,,False,False
C403,10n / 50V X7R / 10%,TDK,C1608X7R1H103K080AA,1,1,Populate,C_0603_1608Metric,top,26.8,53.784909,0,,False,False
C404,1u / 16V X7R / 10%,KEMET / YAGEO,C0603C105K4RACTU,1,1,Populate,C_0603_1608Metric,top,32.5,54.48491,0,,False,False
C405,10n / 50V X7R / 10%,TDK,C1608X7R1H103K080AA,1,1,Populate,C_0603_1608Metric,top,32.5,56.08491,0,,False,False
C406,10n / 50V X7R / 10%,TDK,C1608X7R1H103K080AA,1,1,Populate,C_0603_1608Metric,top,30.1,54.48491,90,,False,False
C407,100n / 50V X7R / 10%,TDK,C1608X7R1H104K080AA,1,1,Populate,C_0603_1608Metric,top,31.075,49.98491,0,,False,False
C408,1u / 16V X7R / 10%,KEMET / YAGEO,C0603C105K4RACTU,1,1,Populate,C_0603_1608Metric,top,34.05,49.98491,0,,False,False
C409,1u / 16V X7R / 10%,KEMET / YAGEO,C0603C105K4RACTU,1,1,Populate,C_0603_1608Metric,top,21.199999,57.78491,-90,,False,False
C501,4.7u / 16V X5R / 10%,TDK,C1608X5R1C475K080AC,1,1,Populate,C_0603_1608Metric,top,23.9,70.18491,0,,False,False
C502,4.7u / 16V X5R / 10%,TDK,C1608X5R1C475K080AC,1,1,Populate,C_0603_1608Metric,top,23.9,64.18491,0,,False,False
C504,100n / 50V X7R / 10%,TDK,C1608X7R1H104K080AA,1,1,Populate,C_0603_1608Metric,top,28.4,69.58491,0,,False,False
C505,1u / 16V X7R / 10%,KEMET / YAGEO,C0603C105K4RACTU,1,1,Populate,C_0603_1608Metric,top,29.1,72.98491,90,,False,False
C506,10n / 50V X7R / 10%,TDK,C1608X7R1H103K080AA,1,1,Populate,C_0603_1608Metric,top,36.549999,55.50991,90,,False,False
C507,10n / 50V X7R / 10%,TDK,C1608X7R1H103K080AA,1,1,Populate,C_0603_1608Metric,top,26.55,59.58491,90,,False,False
C508,100n / 50V X7R / 10%,TDK,C1608X7R1H104K080AA,1,1,Populate,C_0603_1608Metric,top,35.4,59.88491,0,,False,False
C509,1u / 16V X7R / 10%,KEMET / YAGEO,C0603C105K4RACTU,1,1,Populate,C_0603_1608Metric,top,32.15,59.88491,0,,False,False
C601,1u / 25V X7R / 10%,TDK,C2012X7R1E105K125AB,1,1,Populate,C_0805_2012Metric,top,39.4,63.58491,0,,False,False
C701,22u / 25V X5R / 20%,TDK,C3216X5R1E226M160AB,1,1,Populate,C_1206_3216Metric,top,35,71.98491,90,,False,False
C702,22u / 16V X5R / 20%,TDK,C2012X5R1C226M125AC,1,1,Populate,C_0805_2012Metric,top,40.775,77.95,180,,False,False
C703,22u / 16V X5R / 20%,TDK,C2012X5R1C226M125AC,1,1,Populate,C_0805_2012Metric,top,39.15,82.78491,90,,False,False
C704,1u / 25V X7R / 10%,TDK,C2012X7R1E105K125AB,1,1,Populate,C_0805_2012Metric,top,22.15,78.48491,90,,False,False
C705,1u / 25V X7R / 10%,TDK,C2012X7R1E105K125AB,1,1,Populate,C_0805_2012Metric,top,23.95,81.98491,0,,False,False
C707,100n / 50V X7R / 10%,KEMET / YAGEO,C0805C104K5RACTU,1,1,Populate,C_0805_2012Metric,top,41.6,90.40991,90,,False,False
C708,100n / 50V X7R / 10%,KEMET / YAGEO,C0805C104K5RACTU,1,1,Populate,C_0805_2012Metric,top,23.95,84.23491,0,,False,False
C801,100n / 50V X7R / 10%,TDK,C1608X7R1H104K080AA,1,1,Populate,C_0603_1608Metric,top,25.65,79.48491,0,,False,False
C802,100n / 50V X7R / 10%,TDK,C1608X7R1H104K080AA,1,1,Populate,C_0603_1608Metric,top,34.7,78.98491,0,,False,False
C803,33n / 50V X7R / 10%,KEMET / YAGEO,C0805C333K5RACTU,1,1,Populate,C_0805_2012Metric,top,32.15,90.83491,0,,False,False
C804,1u / 16V X7R / 10%,KEMET / YAGEO,C0603C105K4RACTU,1,1,Populate,C_0603_1608Metric,top,36.9,86.48491,0,,False,False
D901,TPD1E10B06DYAR,Texas Instruments,TPD1E10B06DYAR,1,1,Populate,TI_DYA0002A,top,16.7,111.88491,0,Integrated main PCB 2.0,False,False
J103,PACK NTC: 103AT-2,Harwin,M20-9990246,1,1,Populate,PinHeader_1x02_P2.54mm_Vertical,top,23.9,99.20991,0,PROVISIONAL: verify exact purchased part before fabrication; New standard2.54mm PCB header; custom sensor/button/NTC harness; actual remote cable polarity/mate remains measured,False,False
J104,ARM: OPEN,Harwin,M20-9990246,1,1,Populate,PinHeader_1x02_P2.54mm_Vertical,top,23.9,91.20991,0,Fit header; do not fit shunt before commissioning; New standard2.54mm PCB header; custom sensor/button/NTC harness; actual remote cable polarity/mate remains measured; Fit header only; no charging-arm shunt. Keep OPEN pending commissioning.,False,False
J301,GUITION JP1 / 2x13,Samtec,HTSW-113-07-L-D-007,1,1,Populate,Samtec_HTSW-113-07-L-D-007_P2.54mm_Key7,top,47.165,90.72991,180,"Drawing-derived keyed option; exact configured availability requires supplier confirmation. Pin7 post omitted; do not manually remove a header pin without a manufacturer-approved procedure.; Drawing-derived keyed header and IDSD-13-S-04.00-G-P07 gold mate. Exact configured orderability, physical harness and remote connector require qualification.",False,False
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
